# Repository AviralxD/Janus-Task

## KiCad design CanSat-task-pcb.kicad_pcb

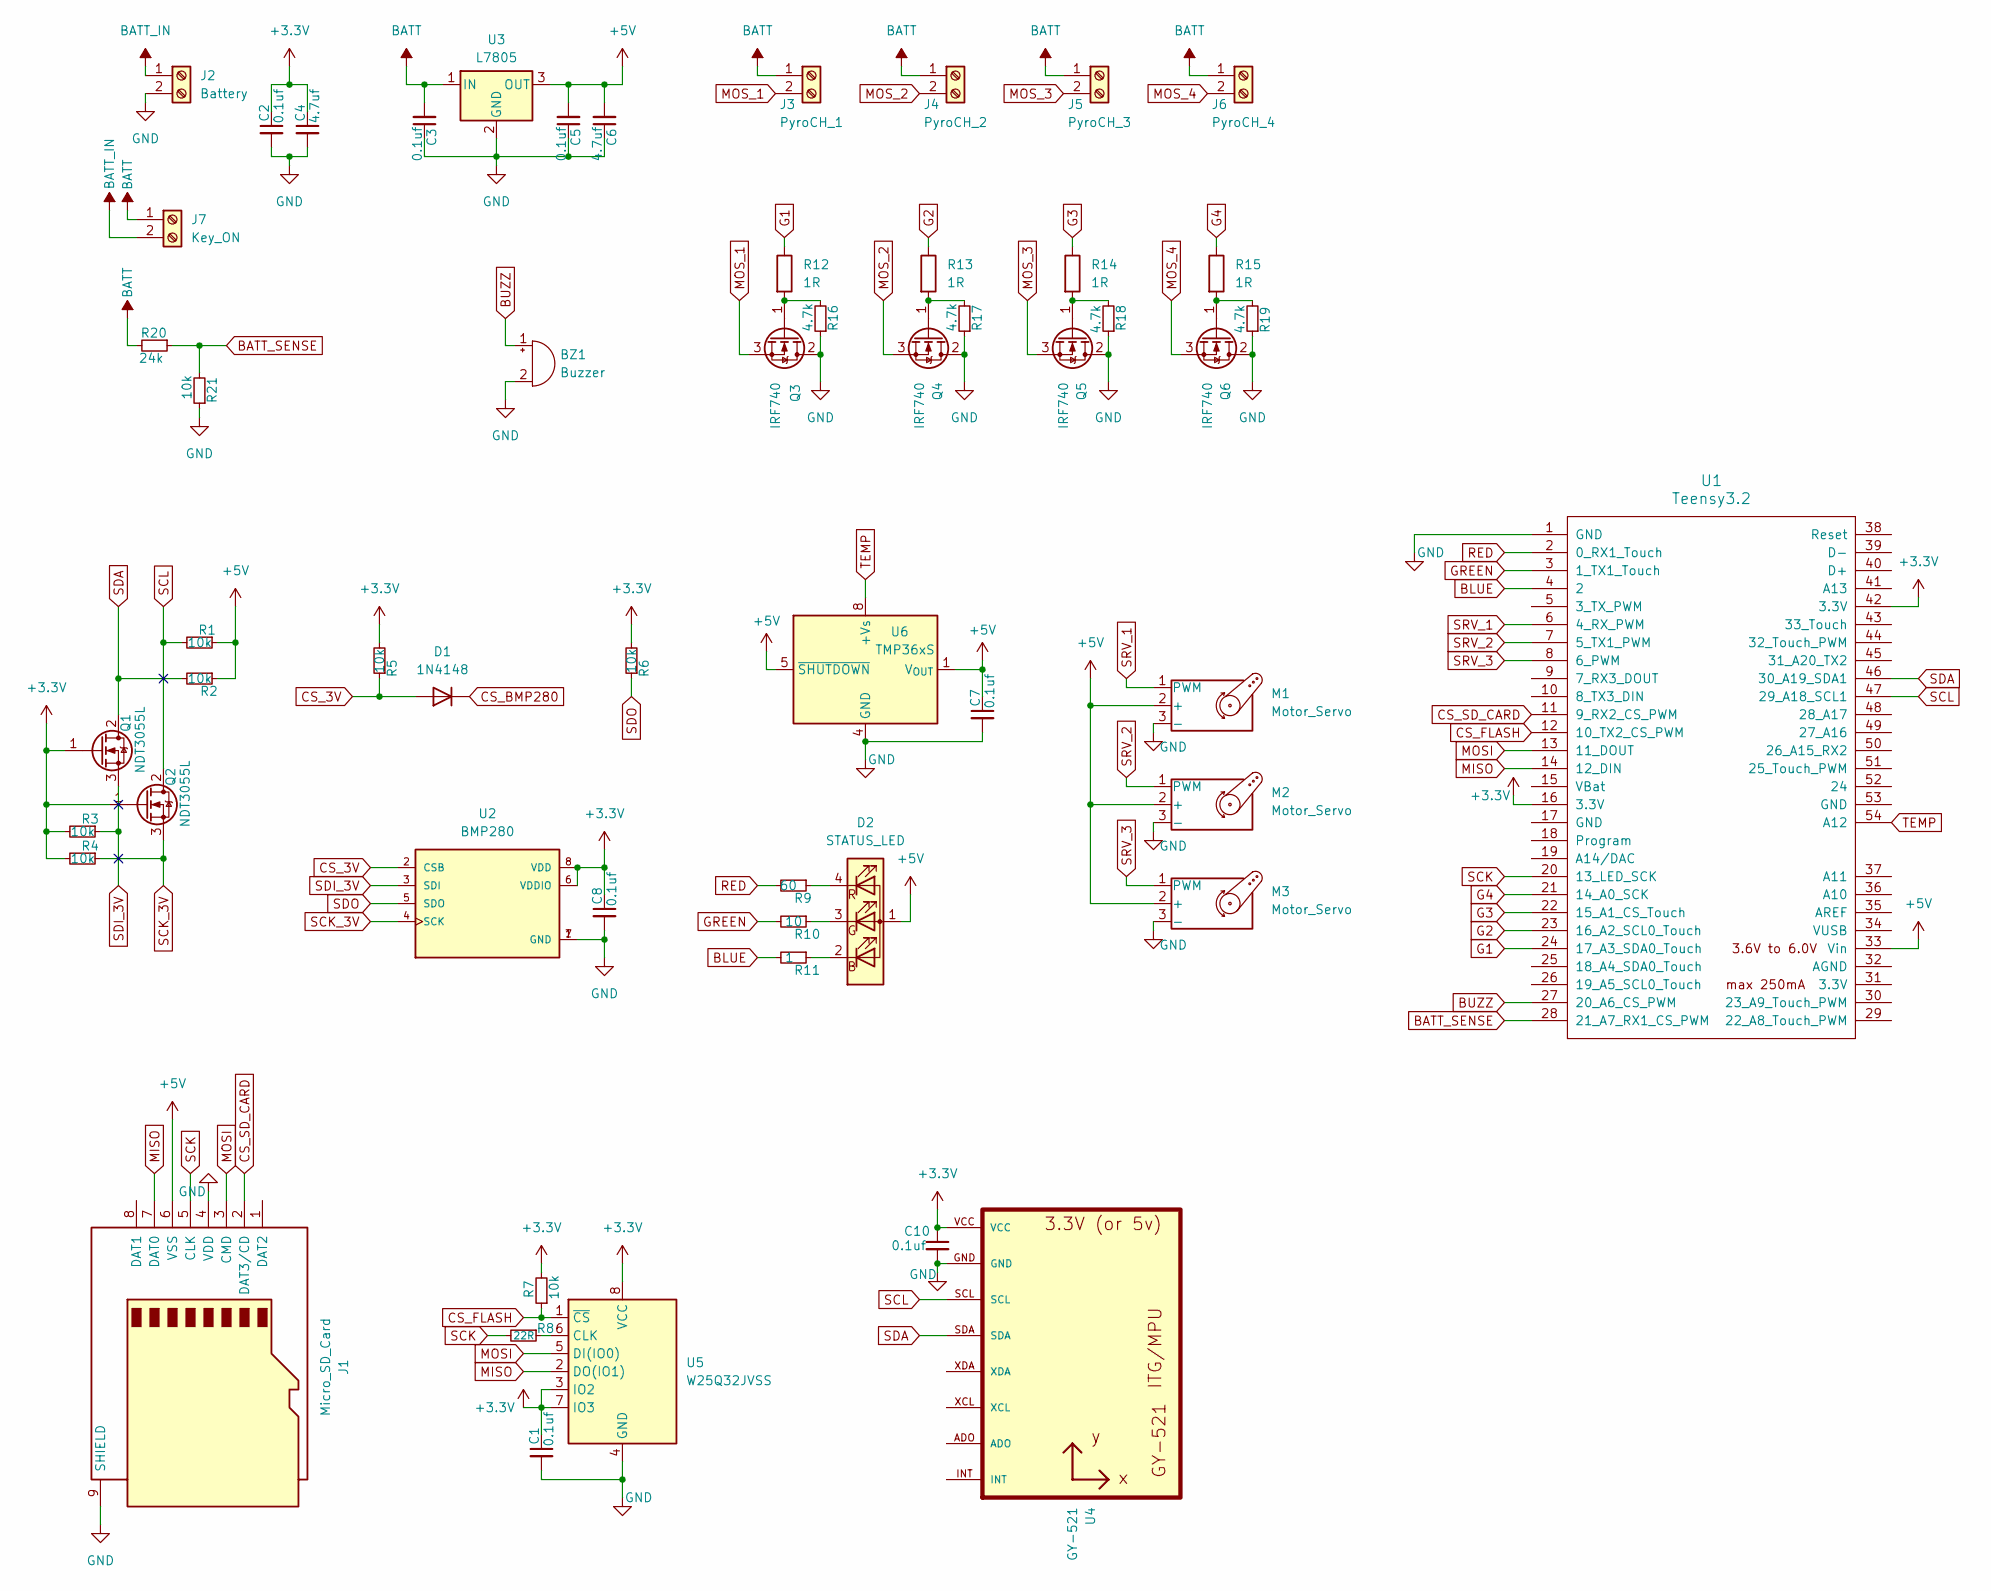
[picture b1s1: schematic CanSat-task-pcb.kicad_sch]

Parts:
BZ1: Buzzer; Buzzer_12x9.5RM7.6
C1, C2, C3, C5, C7, C8, C10: 0.1uf; C_0603_1608Metric
C4, C6: 4.7uf; C_0603_1608Metric
D1: 1N4148; D_DO-35_SOD27_P7.62mm_Horizontal
D2: STATUS_LED; LED_Avago_PLCC4_3.2x2.8mm_CW
J1: Micro_SD_Card; microSD_HC_Molex_47219-2001
J2: Battery; TerminalBlock_4Ucon_1x02_P3.50mm_Horizontal
J3: PyroCH_1; TerminalBlock_4Ucon_1x02_P3.50mm_Horizontal
J4: PyroCH_2; TerminalBlock_4Ucon_1x02_P3.50mm_Horizontal
J5: PyroCH_3; TerminalBlock_4Ucon_1x02_P3.50mm_Horizontal
J6: PyroCH_4; TerminalBlock_4Ucon_1x02_P3.50mm_Horizontal
J7: Key_ON; TerminalBlock_4Ucon_1x02_P3.50mm_Horizontal
M1, M2, M3: Motor_Servo; FanPinHeader_1x03_P2.54mm_Vertical
Q1, Q2: NDT3055L; SOT-223-3_TabPin2
Q3, Q4, Q5, Q6: IRF740; TO-220-3_Vertical
R1, R2, R3, R4, R5, R6, R7, R21: 10k; R_0603_1608Metric
R8: 22R; R_0603_1608Metric
R9: 60; R_0603_1608Metric
R10: 10; R_0603_1608Metric
R11: 1; R_0603_1608Metric
R12, R13, R14, R15: 1R; R_Axial_DIN0309_L9.0mm_D3.2mm_P12.70mm_Horizontal
R16, R17, R18, R19: 4.7k; R_0603_1608Metric
R20: 24k; R_0603_1608Metric
U1: Teensy3.2; Teensy30_31_32_All_Pins
U2: BMP280; Bosch_LGA-8_2x2.5mm_P0.65mm_ClockwisePinNumbering; PART_REV 1.19
U3: L7805; TO255P1020X450X2000-3
U4: GY-521
U5: W25Q32JVSS; SOIC-8_5.23x5.23mm_P1.27mm
U6: TMP36xS; SOIC-8_3.9x4.9mm_P1.27mm

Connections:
+3.3V: C1.1, C2.1, C4.1, C8.1, C10.1, Q1.1 (G), Q2.1 (G), R3.2, R4.2, R5.2, R6.2, R7.2, U1.16 (3.3V), U1.42 (3.3V), U2.6 (VDDIO), U2.8 (VDD), U4.VCC, U5.3 (IO2), U5.7 (IO3), U5.8 (VCC)
+5V: C5.2, C6.2, C7.1, D2.1 (A), J1.6 (VSS), M1.2 (+), M2.2 (+), M3.2 (+), R1.1, R2.1, U1.33 (Vin), U3.3 (OUT), U6.1 (V_{OUT}), U6.5 (~SHUTDOWN)
BATT: C3.2, J3.1, J4.1, J5.1, J6.1, J7.1, R20.2, U3.1 (IN)
BATT_IN: J2.1, J7.2
BATT_SENSE: R20.1, R21.2, U1.28 (21_A7_RX1_CS_PWM)
BLUE: R11.2, U1.4 (2)
BUZZ: BZ1.1 (+), U1.27 (20_A6_CS_PWM)
CS_3V: D1.2 (A), R5.1, U2.2 (CSB)
CS_BMP280: D1.1 (K)
CS_FLASH: R7.1, U1.12 (10_TX2_CS_PWM), U5.1 (~CS)
CS_SD_CARD: J1.2 (DAT3/CD), U1.11 (9_RX2_CS_PWM)
G1: R12.1, U1.24 (17_A3_SDA0_Touch)
G2: R13.1, U1.23 (16_A2_SCL0_Touch)
G3: R14.1, U1.22 (15_A1_CS_Touch)
G4: R15.1, U1.21 (14_A0_SCK)
GND: BZ1.2 (-), C1.2, C2.2, C3.1, C4.2, C5.1, C6.1, C7.2, C8.2, C10.2, J1.4 (VDD), J1.9 (SHIELD), J2.2, M1.3 (-), M2.3 (-), M3.3 (-), Q3.2 (D), Q4.2 (D), Q5.2 (D), Q6.2 (D), R16.1, R17.1, R18.1, R19.1, R21.1, U1.1 (GND), U2.1 (GND), U2.7 (GND), U3.2 (GND), U4.GND, U5.4 (GND), U6.4 (GND)
GREEN: R10.2, U1.3 (1_TX1_Touch)
MISO: J1.7 (DAT0), U1.14 (12_DIN), U5.2 (DO(IO1))
MOSI: J1.3 (CMD), U1.13 (11_DOUT), U5.5 (DI(IO0))
MOS_1: J3.2, Q3.3 (S)
MOS_2: J4.2, Q4.3 (S)
MOS_3: J5.2, Q5.3 (S)
MOS_4: J6.2, Q6.3 (S)
unnamed: D2.2 (BK), R11.1
unnamed: D2.3 (GK), R10.1
unnamed: D2.4 (RK), R9.1
unnamed: Q3.1 (G), R12.2, R16.2
unnamed: Q4.1 (G), R13.2, R17.2
unnamed: Q5.1 (G), R14.2, R18.2
unnamed: Q6.1 (G), R15.2, R19.2
unnamed: R8.1, U5.6 (CLK)
RED: R9.2, U1.2 (0_RX1_Touch)
SCK: J1.5 (CLK), R8.2, U1.20 (13_LED_SCK)
SCK_3V: Q2.3 (S), R4.1, U2.4 (SCK)
SCL: Q2.2 (D), R1.2, U1.47 (29_A18_SCL1), U4.SCL
SDA: Q1.2 (D), R2.2, U1.46 (30_A19_SDA1), U4.SDA
SDI_3V: Q1.3 (S), R3.1, U2.3 (SDI)
SDO: R6.1, U2.5 (SDO)
SRV_1: M1.1 (PWM), U1.6 (4_RX_PWM)
SRV_2: M2.1 (PWM), U1.7 (5_TX1_PWM)
SRV_3: M3.1 (PWM), U1.8 (6_PWM)
TEMP: U1.54 (A12), U6.8 (+Vs)

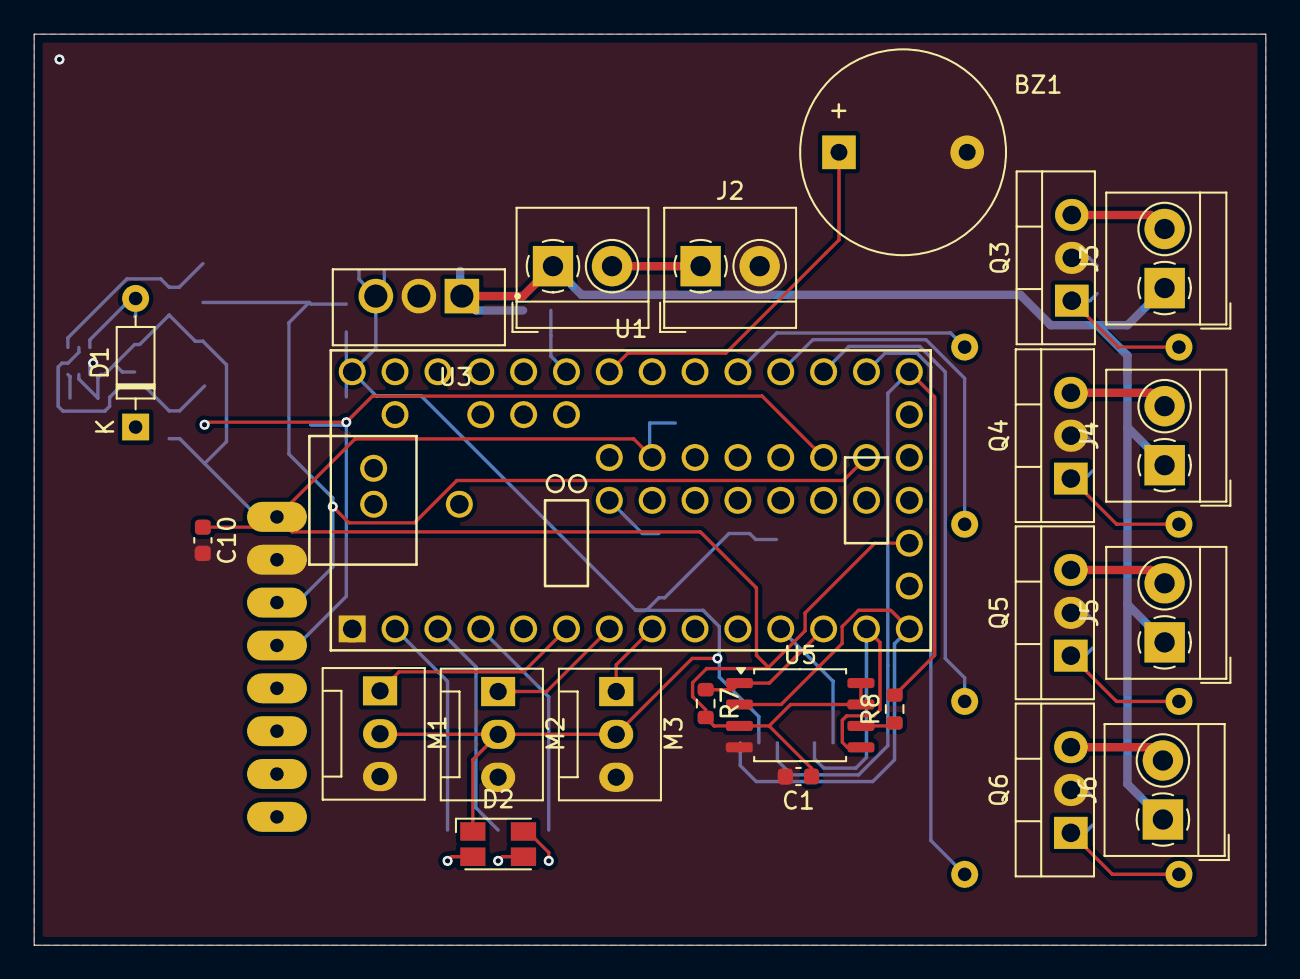
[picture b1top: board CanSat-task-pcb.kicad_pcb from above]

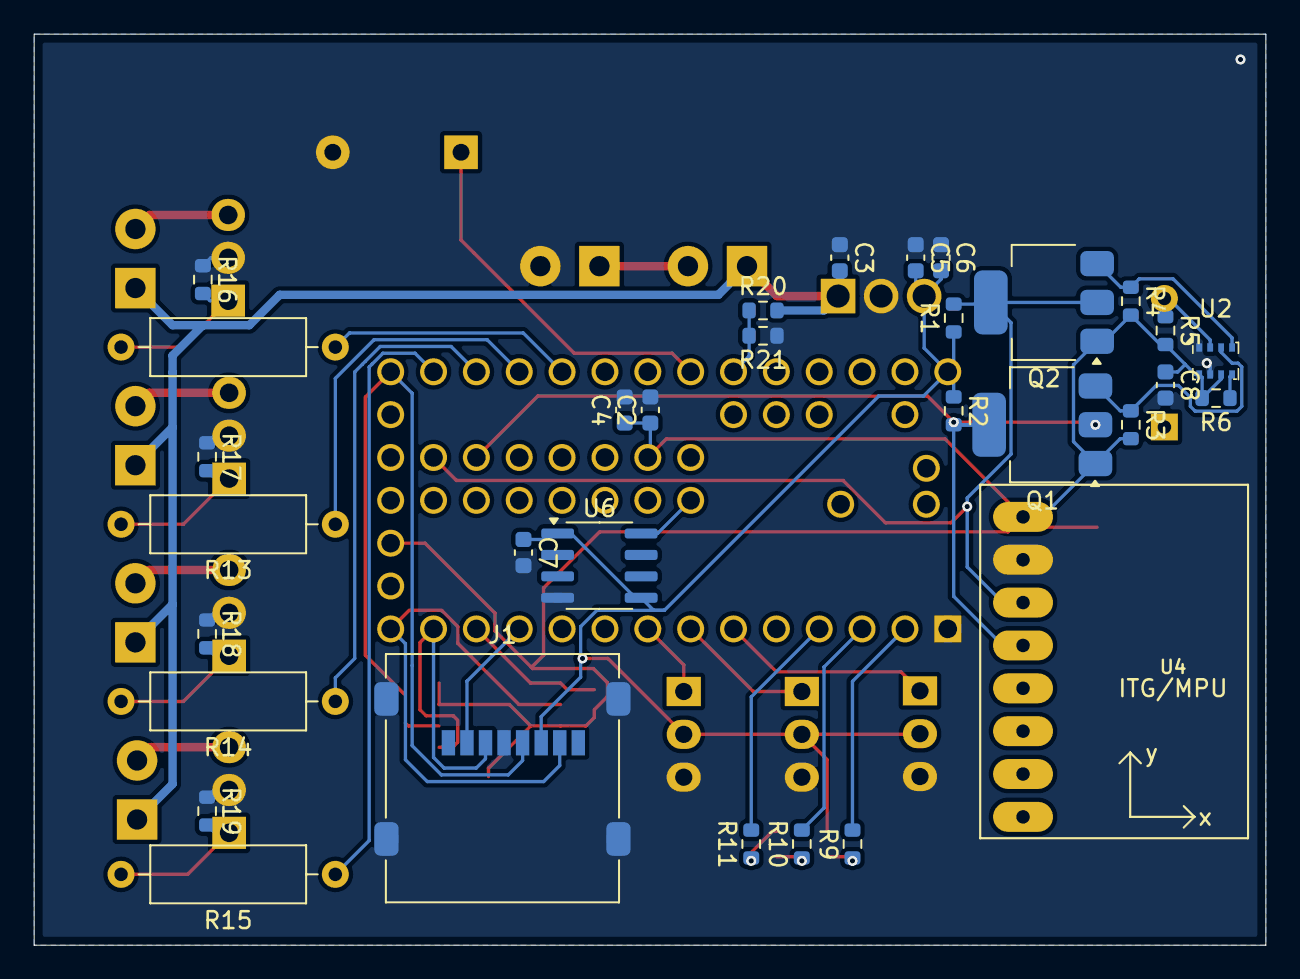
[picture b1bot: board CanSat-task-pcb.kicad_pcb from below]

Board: 2 copper layers, 73.0 x 54.0 mm, 55 parts (32 on the bottom side), 41 nets.
